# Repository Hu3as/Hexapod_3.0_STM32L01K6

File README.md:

## <div align="center">Hexapod Based on STM32 Microcontroller</div>

Designed and built for an engineering thesis, this six-legged walking robot is controlled via Bluetooth or an nRF module. As part of the project, a PCB was designed and fabricated, and the software was developed. The robot's structure was 3D printed.

The repository includes KiCad files for the PCB and a project in STM Cube IDE.

<div style="text-align: center;">

</div>

### Components used:

- <b>Microcontroller:</b> STM32 L031K6T6

- <b>PWM Driver:</b> PCA9685PW

- <b>Bluetooth:</b> HC-05

- <b>nRF:</b> NRF24L01+ 2.4GHz

- <b>Buck Converters:</b> 8.4V → 6V

- <b>Transistors, Regulators, resistors, capacitors and other primary electronic components</b>

- <b>PWM Servos:</b> MG90S

<div style="text-align: center;">

</div>

### <div align="center">Software </div>

The software operates through communication via I2C, SPI, and UART with the respective components: the PWM driver, nRF module, and Bluetooth. The software includes an algorithm responsible for moving the robot's legs in Cartesian space. The robot is capable of moving forward, backward, and rotating.

### Software Structure:

<div style="text-align: center;">

</div>

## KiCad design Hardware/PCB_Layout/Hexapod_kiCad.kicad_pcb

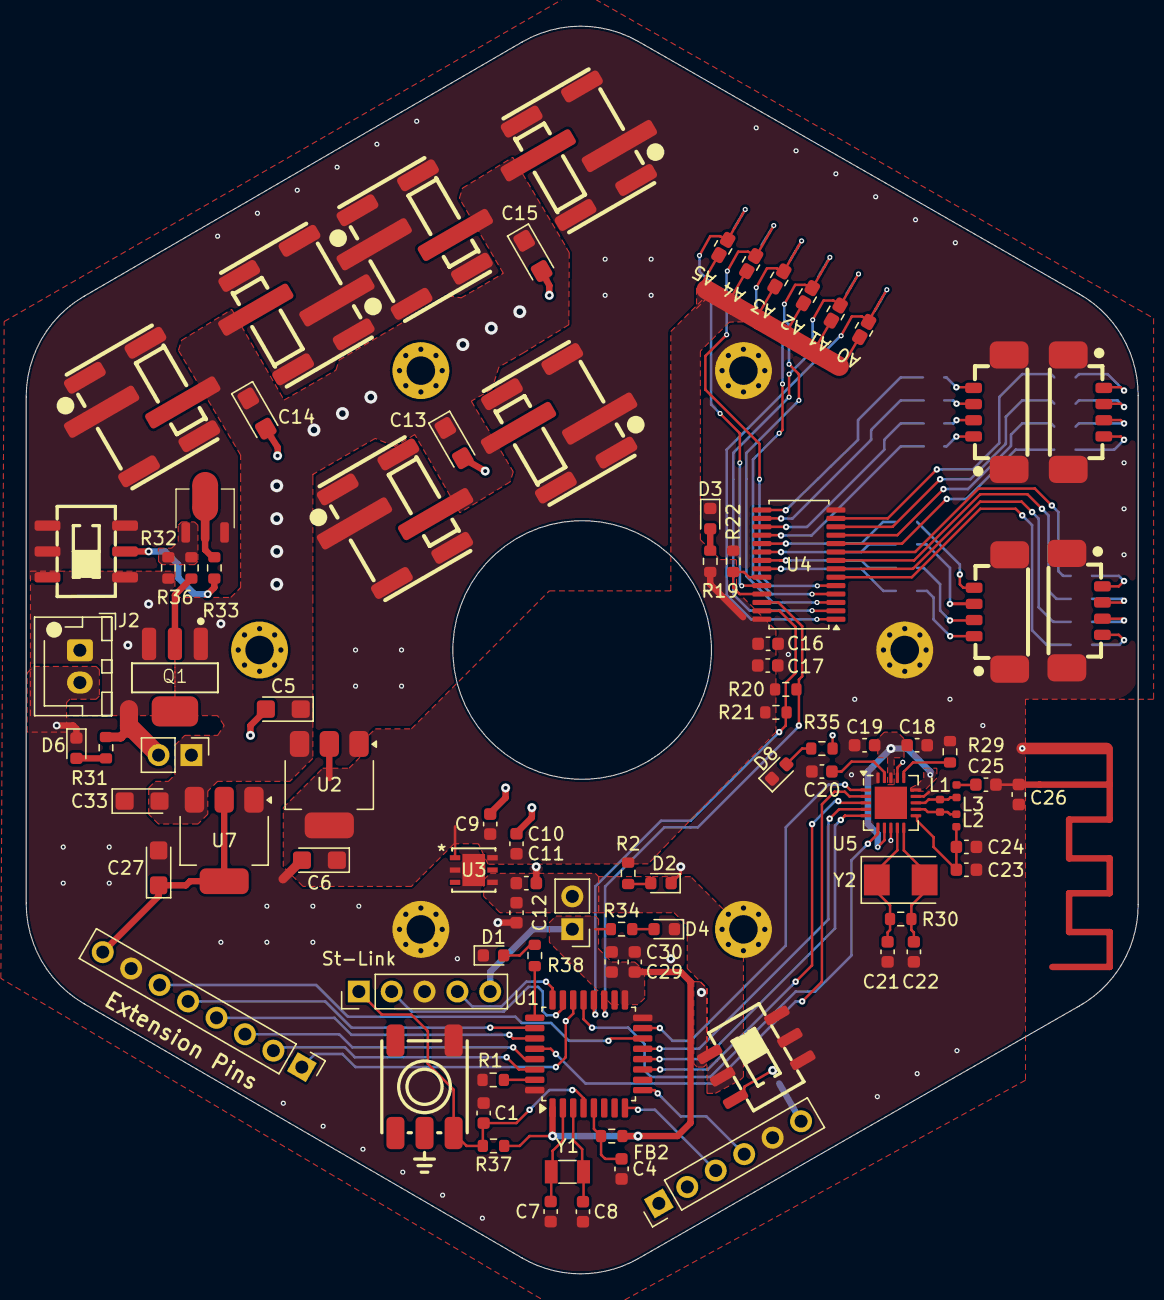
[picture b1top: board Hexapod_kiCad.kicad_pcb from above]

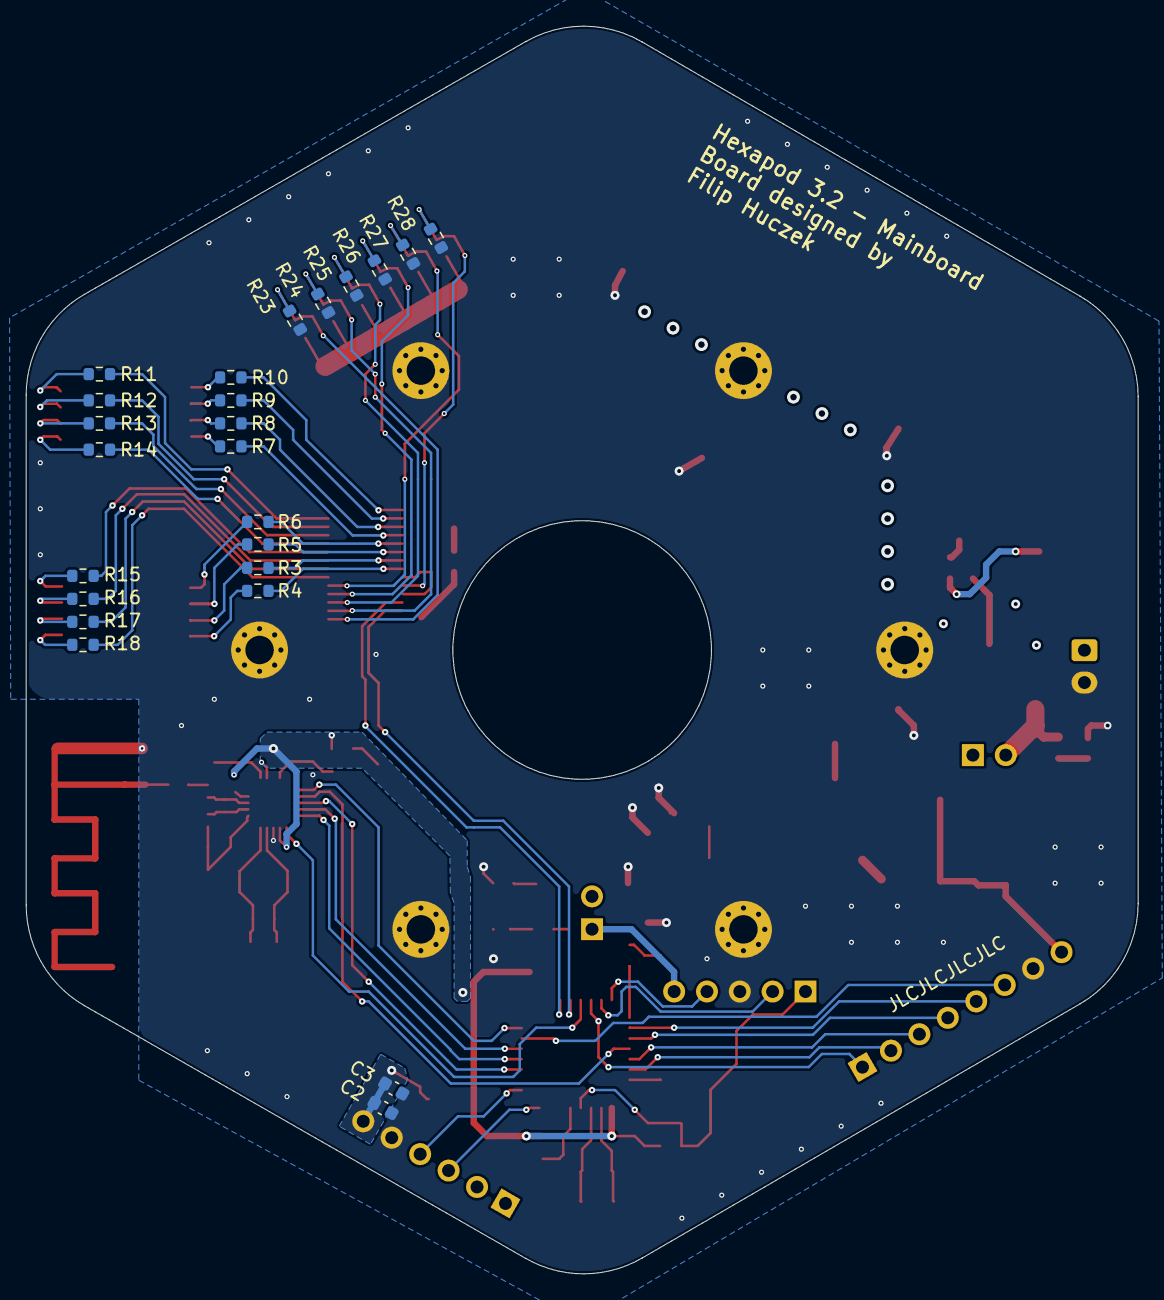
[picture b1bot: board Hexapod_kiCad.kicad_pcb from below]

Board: 2 copper layers, 86.0 x 96.5 mm, 119 parts (24 on the bottom side), 89 nets.

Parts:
C1, C4, C7, C8, C10, C12, C16, C29, C30: 100nF; C_0603_1608Metric
C2, C17, C19: 10nF; C_0603_1608Metric
C3, C18: 1nF; C_0603_1608Metric
C5, C6, C27, C33: 10uF; CP_EIA-3216-18_Kemet-A
C9, C11: 1uF; C_0603_1608Metric
C13, C14, C15: 220nF; CP_EIA-3216-18_Kemet-A
C20: 33nF; C_0603_1608Metric
C21, C22: 22pF; C_0603_1608Metric
C23: 2.2pF; C_0603_1608Metric
C24: 4.7pF; C_0603_1608Metric
C25: 1.5pF; C_0603_1608Metric
C26: 10pF; C_0603_1608Metric
D1: AsUWish; LED_0603_1608Metric
D2: Red; LED_0603_1608Metric
D3: Emerald; LED_0603_1608Metric
D4: Purple; LED_0603_1608Metric
D6: Blue; LED_0603_1608Metric
D8: Amber; LED_0603_1608Metric
FB2: 1kΩ@100MHz; R_0603_1608Metric
H1, H2, H3, H4, H5, H6: MountingHole_Pad; MountingHole_2.2mm_M2_Pad_Via_withoutCourtyard
J1, J3, J12, J13, J14, J15: Servo_Power; Servo_Power_header
J2: Main_PWR_7.4V; JST_XH_B2B-XH-AM_1x02_P2.50mm_Vertical
J4: 01x06_Socket_Bluetooth; PinHeader_1x06_P2.54mm_Vertical
J5, J16: Power_jumper; PinHeader_1x02_P2.54mm_Vertical
J6, J7, J8, J9: Conn_01x04_Pin_Servo_PWM; Picoblade_1.25_footprint
J10: Conn_01x08_Pin; PinHeader_1x08_P2.54mm_Vertical
JP2, JP3, JP4, JP9, JP11, JP13: SolderJumper_2_Open; R_0603_1608Metric
L1: 8.2nH; L_0402_1005Metric
L2: 2.7nH; L_0402_1005Metric
L3: 3.9nH; L_0402_1005Metric
Q1: PMOS; PMOS_BSP170P-VB
Q3: NPN; 2N2222AU
R1, R20, R21, R22, R23, R24, R25, R26, R27, R28, R32, R33, R37: 10k; R_0603_1608Metric
R2: 150; R_0603_1608Metric
R3, R4, R5, R6, R7, R8, R9, R10, R11, R12, R13, R14, R15, R16, R17, R18, R35: 220; R_0603_1608Metric
R19, R34, R36: 100; R_0603_1608Metric
R29: 22k; R_0603_1608Metric
R30: 1M; R_0603_1608Metric
R31: 200; R_0603_1608Metric
R38: AsUWish; R_0603_1608Metric
S1, S2: 452403012014; Slider_G-Switch MS-22D28-G020_footprint
SW1: SW_Push; Reset_Button
St-Link: Conn_01x05_Pin; PinHeader_1x05_P2.54mm_Vertical
U1: STM32L031K6Tx; LQFP-32_7x7mm_P0.8mm
U2, U7: LD1117S50TR_SOT223; SOT-223-3_TabPin2
U3: LD39050PU33R; DFN6_3X3_STM
U4: PCA9685PW; TSSOP-28_4.4x9.7mm_P0.65mm
U5: nRF24L01P; QFN-20-1EP_4x4mm_P0.5mm_EP2.5x2.5mm
Y1: 32.768KHz; Crystal_SMD_3215-2Pin_3.2x1.5mm
Y2: 16M; Crystal_SMD_5032-2Pin_5.0x3.2mm

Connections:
7.4V: J2.1, J5.2, Q1.3 (S), R31.1, R32.1, S1.3
+3.3V: C11.2, C12.2, C29.2, C30.2, FB2.2, J16.1, J16.2, R34.1, R37.1, S2.2, St-Link.5, U1.1 (VDD), U1.17 (VDD), U3.4 (VOUT)
+5V: C6.1, C9.1, C10.1, C16.2, C17.2, JP2.2 (B), JP3.2 (B), JP4.2 (B), JP9.2 (B), JP11.2 (B), JP13.2 (B), R2.1, R19.1, R20.2, R21.2, U2.2 (VO), U3.1 (EN), U3.6 (VIN), U4.28 (VDD)
+5_EXT: C27.1, J10.8, U7.2 (VO)
/Driver/BL_3.3V: C2.2, C3.1, J4.6, S2.1
/Driver/NRF_3.3V: C18.1, C19.2, R35.1, S2.3, U5.7 (VDD), U5.15 (VDD), U5.18 (VDD)
/Q3_C: Q3.1 (C), R32.2, R36.2
BTH_Rx: J4.4, U1.9 (PA3)
BTH_Tx: J4.3, U1.8 (PA2)
CE: U1.15 (PB1), U5.1 (CE)
CSN: U1.28 (PB5), U5.2 (CSN)
GND: C1.1, C2.1, C3.2, C4.2, C5.2, C6.2, C7.1, C8.1, C9.2, C10.2, C11.1, C12.1, C13.2, C14.2, C15.2, C16.1, C17.1, C18.2, C19.1, C20.2, C21.2, C22.2, C23.2, C24.2, C25.2, C26.1, C26.2, C27.2, C29.1, C30.1, C33.1, D1.1 (K), D2.1 (K), D3.1 (K), D4.1 (K), D6.1 (K), D8.1 (K), H1.1, H2.1, H3.1, H4.1, H5.1, H6.1, J1.1, J1.3, J1.4, J1.5, J1.6, J2.2, J3.1, J3.3, J3.4, J3.5, J3.6, J4.5, J6.5, J6.6, J7.5, J7.6, J8.5, J8.6, J9.5, J9.6, J10.7, J12.1, J12.3, J12.4, J12.5, J12.6, J13.1, J13.3, J13.4, J13.5, J13.6, J14.1, J14.3, J14.4, J14.5, J14.6, J15.1, J15.3, J15.4, J15.5, J15.6, Q3.3 (E), R1.2, R22.1, R23.1, R24.1, R25.1, R26.1, R27.1, R28.1, R29.2, S1.1, S1.4, S1.5, S1.6, S2.4, S2.5, S2.6, SW1.1, St-Link.3, U1.16 (VSS), U1.32 (VSS), U2.1 (GND), U3.2 (GND), U3.7 (GND), U4.14 (VSS), U5.8 (VSS), U5.14 (VSS), U5.17 (VSS), U5.20 (VSS), U7.1 (GND)
IRQ: U1.21 (PA11), U5.6 (IRQ)
NRST: C1.2, R37.2, SW1.2, St-Link.1, U1.4 (NRST)
unnamed: C25.1, L3.1
unnamed: D1.2 (A), R38.2
unnamed: D2.2 (A), R2.2
unnamed: D3.2 (A), R19.2
unnamed: D4.2 (A), R34.2
unnamed: D6.2 (A), R31.2
unnamed: D8.2 (A), R35.2
unnamed: J6.1, R7.2
unnamed: J6.2, R8.2
unnamed: J6.3, R9.2
unnamed: J6.4, R10.2
unnamed: J7.1, R4.2
unnamed: J7.2, R3.2
unnamed: J7.3, R5.2
unnamed: J7.4, R6.2
unnamed: J8.1, R11.2
unnamed: J8.2, R12.2
unnamed: J8.3, R13.2
unnamed: J8.4, R14.2
unnamed: J9.1, R15.2
unnamed: J9.2, R16.2
unnamed: J9.3, R17.2
unnamed: J9.4, R18.2
unnamed: JP2.1 (A), R23.2, U4.1 (A0)
unnamed: JP3.1 (A), R24.2, U4.2 (A1)
unnamed: JP4.1 (A), R25.2, U4.3 (A2)
unnamed: JP9.1 (A), R26.2, U4.4 (A3)
unnamed: JP11.1 (A), R27.2, U4.5 (A4)
unnamed: JP13.1 (A), R28.2, U4.24 (A5)
unnamed: Q1.2 (G), R36.1
unnamed: Q3.2 (B), R33.1
unnamed: R33.2, S1.2
unnamed: R1.1, U1.31 (BOOT0)
unnamed: R38.1, U1.25 (PA15)
unnamed: C7.2, U1.2 (PC14), Y1.2
unnamed: C8.2, U1.3 (PC15), Y1.1
unnamed: R22.2, U4.23 (~OE), U4.25 (EXTCLK)
unnamed: R18.1, U4.6 (LED0)
unnamed: R17.1, U4.7 (LED1)
unnamed: R16.1, U4.8 (LED2)
unnamed: R15.1, U4.9 (LED3)
unnamed: R14.1, U4.10 (LED4)
unnamed: R13.1, U4.11 (LED5)
unnamed: R12.1, U4.12 (LED6)
unnamed: R11.1, U4.13 (LED7)
unnamed: R10.1, U4.15 (LED8)
unnamed: R9.1, U4.16 (LED9)
unnamed: R8.1, U4.17 (LED10)
unnamed: R7.1, U4.18 (LED11)
unnamed: R6.1, U4.19 (LED12)
unnamed: R5.1, U4.20 (LED13)
unnamed: R3.1, U4.21 (LED14)
unnamed: R4.1, U4.22 (LED15)
unnamed: L1.2, L2.2, U5.12 (ANT1)
unnamed: L1.1, L3.2, U5.13 (ANT2)
unnamed: C20.1, U5.19 (DVDD)
unnamed: R29.1, U5.16 (IREF)
unnamed: C23.1, C24.1, L2.1, U5.11 (VDD_PA)
unnamed: C22.1, R30.1, U5.10 (XC1), Y2.2
unnamed: C21.1, R30.2, U5.9 (XC2), Y2.1
Ou1: J10.1, U1.22 (PA12)
Ou2: J10.2, U1.30 (PB7)
Ou3: J10.3, U1.29 (PB6)
Ou4: J10.4, U1.27 (PB4)
Ou5: J10.5, U1.26 (PB3)
Ou6: J10.6, U1.14 (PB0)
SCL: R20.1, U1.19 (PA9), U4.26 (SCL)
SDA: R21.1, U1.20 (PA10), U4.27 (SDA)
SPI_MISO: U1.12 (PA6), U5.5 (MISO)
SPI_MOSI: U1.13 (PA7), U5.4 (MOSI)
SPI_SCK: U1.11 (PA5), U5.3 (SCK)
SWCLK: St-Link.4, U1.24 (PA14)
SWDIO: St-Link.2, U1.23 (PA13)
VDDA: C4.1, FB2.1, U1.5 (VDDA)
Vin: C5.1, C13.1, C14.1, C15.1, C33.2, J1.2, J3.2, J5.1, J12.2, J13.2, J14.2, J15.2, Q1.1 (D), U2.3 (VI), U7.3 (VI)

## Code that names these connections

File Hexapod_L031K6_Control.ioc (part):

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Mcu.Name=STM32L031K(4-6)Tx
Mcu.Package=LQFP32
Mcu.UserName=STM32L031K6Tx
PA10.Mode=I2C
PA10.Signal=I2C1_SDA
PA13.GPIOParameters=GPIO_Label
PA13.GPIO_Label=TMS
PA13.Mode=Serial_Wire
PA13.Signal=SYS_SWDIO
PA14.GPIOParameters=GPIO_Label
PA14.GPIO_Label=TCK
PA14.Mode=Serial_Wire
PA14.Signal=SYS_SWCLK
PA15.Signal=GPIO_Output
PA2.Mode=Asynchronous
PA2.Signal=USART2_TX
PA3.Mode=Asynchronous
PA3.Signal=USART2_RX
PA9.Mode=I2C
PA9.Signal=I2C1_SCL
PB1.Signal=GPIO_Output
PB5.Signal=GPIO_Output
PC14-OSC32_IN.Mode=LSE-External-Oscillator
PC14-OSC32_IN.Signal=RCC_OSC32_IN
PC15-OSC32_OUT.Mode=LSE-External-Oscillator
PC15-OSC32_OUT.Signal=RCC_OSC32_OUT
RCC.HSE_VALUE=8000000
RCC.SYSCLKFreq_VALUE=32000000
RCC.SYSCLKSource=RCC_SYSCLKSOURCE_PLLCLK
board=NUCLEO-L031K6
boardIOC=true

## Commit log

2023-06-21 Alpha Code
2025-01-16 Movement update
2025-02-03 Add files via upload
    Hexapod movement control via Bluetooth & NRF
2025-04-11 thesis desctiption
    Desctiption of hexapod project
2025-04-14 Screens & Hardware Files
2025-04-14 Rename render src
2025-04-14 Update README.md
    Photos of the project have been added
2025-04-14 Update README.md
    little patch
